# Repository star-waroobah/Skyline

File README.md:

# Skyline

Skyline is a custom flight controller for a quadcopter drone using the STM32F722 microcontroller. It will act as the brain of the drone.

I made this as the half life week 5 project.

## Features

- **STM32F722RET6 MCU** with 25 MHz and 32.768 kHz crystals, plus reset and boot buttons
- **USB-C port** for power and programming
- **4 motor outputs** (PA0–PA3) through one 8-pin 4-in-1 ESC header
- **Receiver header** (UART, 3.3 V) for ELRS or similar radios
- **Battery voltage monitoring**, with the divider sized for a 4S battery
- **SWD header** as a backup way to flash firmware
- **Plug-in IMU (SPI) and barometer (I2C) headers** for breakout boards
- **microSD slot** for flight logging
- **Dual power input:** two SS34 diodes let the board run from USB or the battery
- **LMR51430 3.3 V buck regulator** that accepts up to 36 V in
- **Hand-solderable:** 0603 and 0805 parts and 2.54 mm headers

## How it works

It uses an IMU sensor to detect movement and orientation and a barometer to estimate altitude. The board receive commands from a radio receiver and send signals to four ESCs to control the motors and help keep the drone stable. It also have USB-C for connectivity, a microSD card for flight data logging, and battery voltage monitoring. 

## PCB

## Schematic

## 3D View

## Bill of Materials

Full BOM: [`hardware/BOM.csv`](hardware/BOM.csv)

| Part | Qty | Notes |
|------|-----|-------|
| [Microcontroller] | 1 | |
| [IMU / sensor] | 1 | |
| [Motors] | 4 | |
| [ESCs / motor drivers] | 4 | |
| [Battery] | 1 | |
| [Frame] | 1 | |

## Credits

- Symbols and footprints from EasyKiCad2 / EasyEDA converted libraries (included in `hardware/`).
- I also took guidance from the Hack Club guide (https://blueprint.hackclub.com/starter-projects/flightcontroller)

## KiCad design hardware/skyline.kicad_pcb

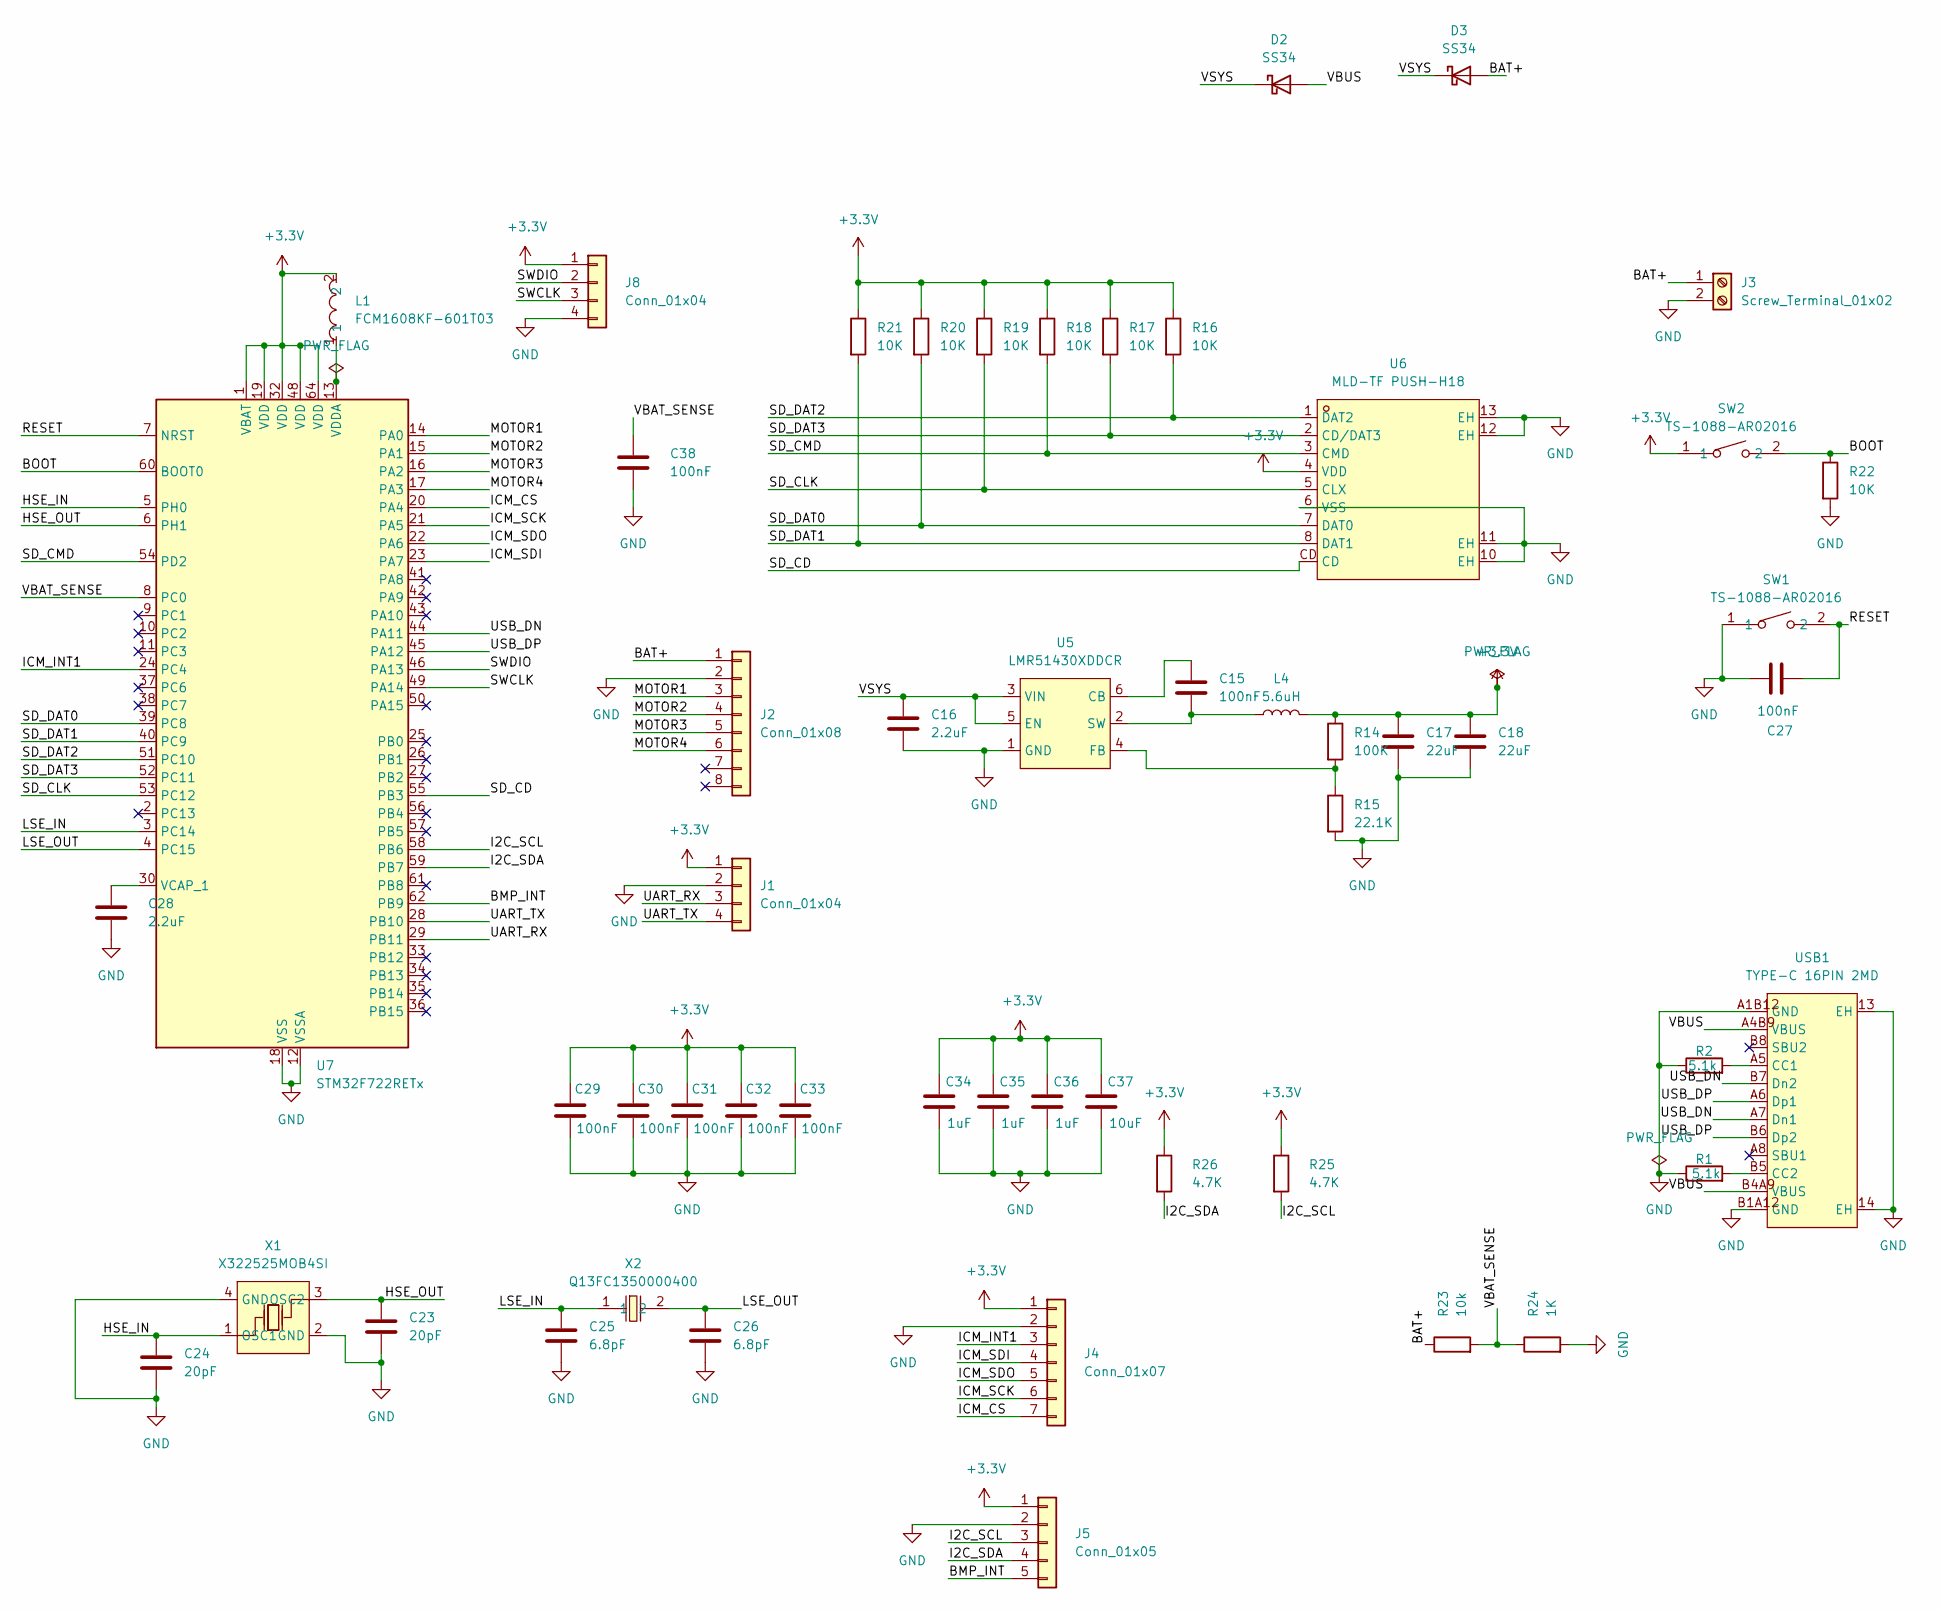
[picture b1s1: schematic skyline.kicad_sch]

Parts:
C15, C27, C29, C30, C31, C32, C33: 100nF; C_0603_1608Metric
C16, C28: 2.2uF; C_0603_1608Metric
C17, C18: 22uF; C_0603_1608Metric
C23, C24: 20pF; C_0603_1608Metric
C25, C26: 6.8pF; C_0603_1608Metric
C34, C35, C36: 1uF; C_0805_2012Metric
C37: 10uF; C_0603_1608Metric
C38: 100nF; C_0805_2012Metric
D2, D3: SS34; D_SMA
J1, J8: Conn_01x04; PinHeader_1x04_P2.54mm_Vertical
J2: Conn_01x08; PinHeader_1x08_P2.54mm_Vertical
J3: Screw_Terminal_01x02; TerminalBlock_Xinya_XY308-2.54-2P_1x02_P2.54mm_Horizontal
J4: Conn_01x07; PinHeader_1x07_P2.54mm_Vertical
J5: Conn_01x05; PinHeader_1x05_P2.54mm_Vertical
L1: FCM1608KF-601T03; L0603; MPN FCM1608KF-601T03; LCSC Part C141723
L4: 5.6uH; IND-SMD_L3.0-W3.0
R1, R2: 5.1k; R_0603_1608Metric
R14: 100K; R_0603_1608Metric
R15: 22.1K; R_0603_1608Metric
R16, R17, R18, R19, R20, R21, R22: 10K; R_0603_1608Metric
R23: 10k; R_0603_1608Metric
R24: 1K; R_0603_1608Metric
R25, R26: 4.7K; R_0603_1608Metric
SW1, SW2: TS-1088-AR02016; SW-SMD_L3.9-W3.0-P4.45; MPN TS-1088-AR02016; LCSC Part C720477
U5: LMR51430XDDCR; SOT-23-6_L2.9-W1.6-P0.95-LS2.8-BL; MPN LMR51430XDDCR; LCSC Part C5185863
U6: MLD-TF PUSH-H18; SD-SMD_MLD-TF-PUSH-H18; MPN MLD-TF PUSH-H18; LCSC Part C52750848
U7: STM32F722RETx; LQFP-64_10x10mm_P0.5mm
USB1: TYPE-C 16PIN 2MD; USB-C-SMD_TYPE-C-16PIN-2MD-073; MPN TYPE-C 16PIN 2MD(073); LCSC Part C2765186
X1: X322525MOB4SI; CRYSTAL-SMD_4P-L3.2-W2.5-BL; MPN X322525MOB4SI; LCSC Part C9006
X2: Q13FC1350000400; FC-135R_L3.2-W1.5; MPN Q13FC13500004; LCSC Part C32346

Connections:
+3.3V: C17.1, C18.1, C29.1, C30.1, C31.1, C32.1, C33.1, C34.1, C35.1, C36.1, C37.1, J1.1, J4.1, J5.1, J8.1, L1.2, L4.2, R14.1, R16.1, R17.1, R18.1, R19.1, R20.1, R21.1, R25.1, R26.1, SW2.1, U6.4 (VDD), U7.1 (VBAT), U7.19 (VDD), U7.32 (VDD), U7.48 (VDD), U7.64 (VDD)
/<NO NET>: D2.2 (A), USB1.A4B9 (VBUS), USB1.B4A9 (VBUS)
/BAT+: D3.2 (A), J2.1, J3.1, R23.1
/BMP_INT: J5.5, U7.62 (PB9)
/BOOT: R22.1, SW2.2, U7.60 (BOOT0)
/HSE_IN: C24.1, U7.5 (PH0), X1.1 (OSC1)
/HSE_OUT: C23.1, U7.6 (PH1), X1.3 (OSC2)
/I2C_SCL: J5.3, R25.2, U7.58 (PB6)
/I2C_SDA: J5.4, R26.2, U7.59 (PB7)
/ICM_CS: J4.7, U7.20 (PA4)
/ICM_INT1: J4.3, U7.24 (PC4)
/ICM_SCK: J4.6, U7.21 (PA5)
/ICM_SDI: J4.4, U7.23 (PA7)
/ICM_SDO: J4.5, U7.22 (PA6)
/LSE_IN: C25.1, U7.3 (PC14), X2.1
/LSE_OUT: C26.1, U7.4 (PC15), X2.2
/MOTOR1: J2.3, U7.14 (PA0)
/MOTOR2: J2.4, U7.15 (PA1)
/MOTOR3: J2.5, U7.16 (PA2)
/MOTOR4: J2.6, U7.17 (PA3)
/RESET: C27.1, SW1.2, U7.7 (NRST)
/SD_CD: U6.CD, U7.55 (PB3)
/SD_CLK: R19.2, U6.5 (CLX), U7.53 (PC12)
/SD_CMD: R18.2, U6.3 (CMD), U7.54 (PD2)
/SD_DAT0: R20.2, U6.7 (DAT0), U7.39 (PC8)
/SD_DAT1: R21.2, U6.8 (DAT1), U7.40 (PC9)
/SD_DAT2: R16.2, U6.1 (DAT2), U7.51 (PC10)
/SD_DAT3: R17.2, U6.2 (CD/DAT3), U7.52 (PC11)
/SWCLK: J8.3, U7.49 (PA14)
/SWDIO: J8.2, U7.46 (PA13)
/UART_RX: J1.3, U7.29 (PB11)
/UART_TX: J1.4, U7.28 (PB10)
/USB_DN: U7.44 (PA11), USB1.A7 (Dn1), USB1.B7 (Dn2)
/USB_DP: U7.45 (PA12), USB1.A6 (Dp1), USB1.B6 (Dp2)
/VBAT_SENSE: C38.1, R23.2, R24.1, U7.8 (PC0)
/VSYS: C16.1, D2.1 (K), D3.1 (K), U5.3 (VIN), U5.5 (EN)
GND: C16.2, C17.2, C18.2, C23.2, C24.2, C25.2, C26.2, C27.2, C28.2, C29.2, C30.2, C31.2, C32.2, C33.2, C34.2, C35.2, C36.2, C37.2, C38.2, J1.2, J2.2, J3.2, J4.2, J5.2, J8.4, R1.1, R2.1, R15.2, R22.2, R24.2, SW1.1, U5.1 (GND), U6.6 (VSS), U6.10 (EH), U6.11 (EH), U6.12 (EH), U6.13 (EH), U7.12 (VSSA), U7.18 (VSS), U7.31 (VSS), U7.47 (VSS), U7.63 (VSS), USB1.13 (EH), USB1.14 (EH), USB1.A1B12 (GND), USB1.B1A12 (GND), X1.2 (GND), X1.4 (GND)
unnamed: C15.1, U5.6 (CB)
unnamed: R14.2, R15.1, U5.4 (FB)
unnamed: C15.2, L4.1, U5.2 (SW)
unnamed: C28.1, U7.30 (VCAP_1)
unnamed: L1.1, U7.13 (VDDA)
unnamed: R2.2, USB1.A5 (CC1)
unnamed: R1.2, USB1.B5 (CC2)

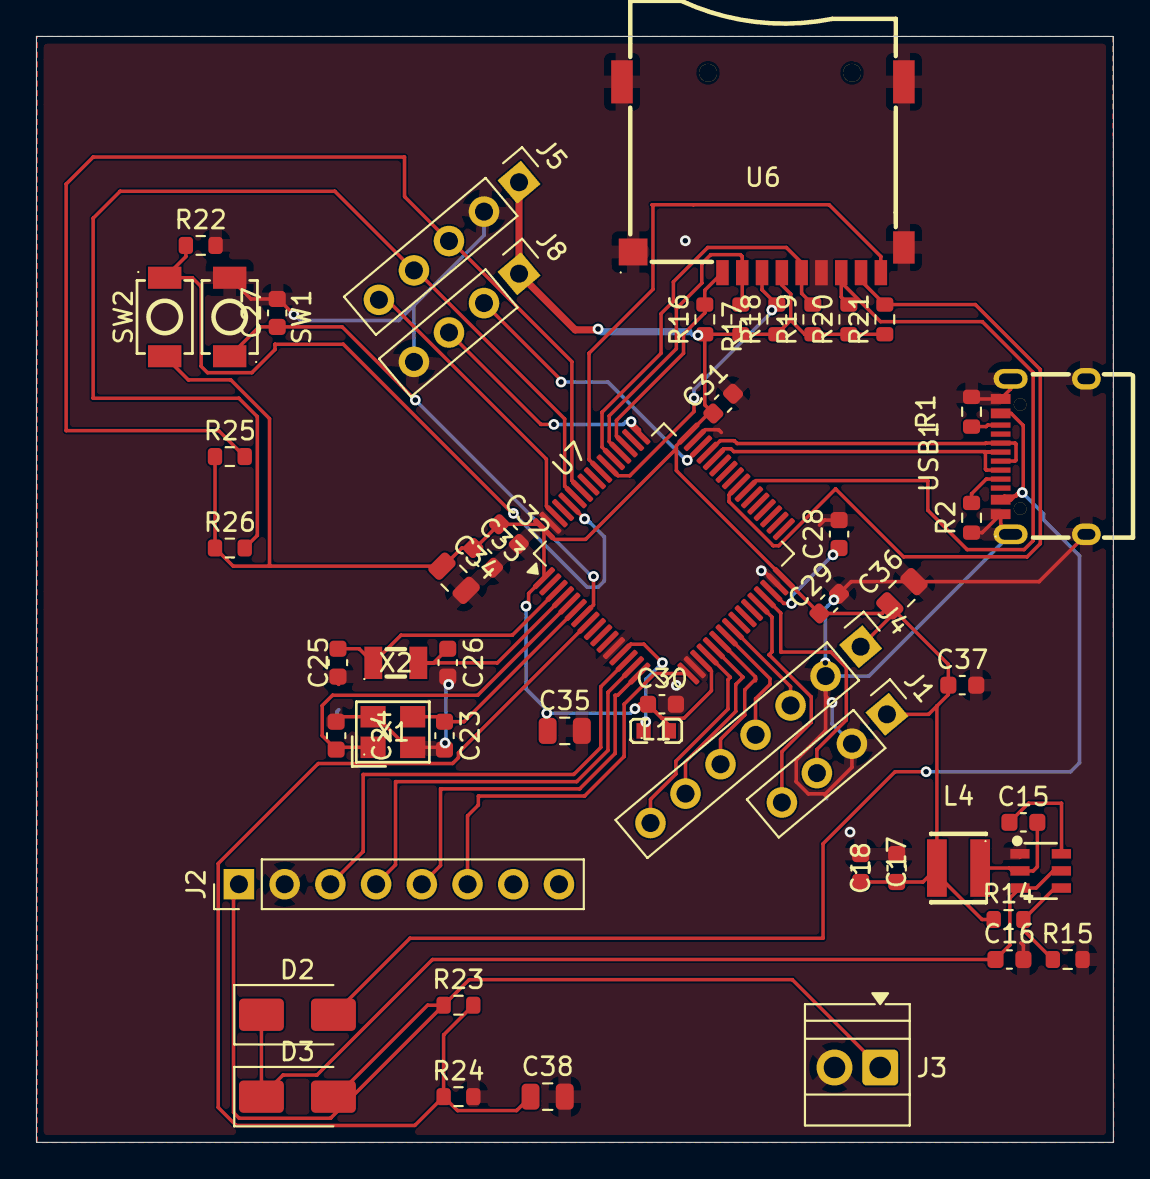
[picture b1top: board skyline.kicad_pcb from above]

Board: 2 copper layers, 59.8 x 61.4 mm, 53 parts (0 on the bottom side), 44 nets.
